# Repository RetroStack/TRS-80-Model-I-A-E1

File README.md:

# TRS-80 Model 1 (Rev A) Replica - E1

This project is a reverse-engineered PCB created to document the mainboard of the iconic TRS-80 Model 1 (Revision A) computer. Released in 1977, Revision A was the first implementation and features some differences compared to later revisions, including a different Z3 selector, a slightly modified video sync circuit, and a lack of support for 8k dynamic RAM.

The entire project is available under the MIT license.

**NOTE:** The PCB has not yet been validated. Once I am able to fully validate the PCB by producing a board and thoroughly testing it, I will make the Gerber files available. Additionally, I will have some PCBs available in my [store](https://shop.retrostack.org).

## Project Details

### Latest Files

In the "Latest" folder, you'll find the most up-to-date design files, including:

- The [full schematics](/Latest/TRS80_Model_I_A_E1_Schematics.pdf) of the E1 replica which is 1:1 to the original G board.

### Implementation

E1 has been implemented using KiCAD 8. The KiCAD project files are included in this repository.

### RetroStack Libraries

To work with this KiCAD project, you'll need the RetroStack libraries for KiCAD. Please [follow this link](https://www.github.com/RetroStack/KiCAD-Libraries) to access and install these libraries.

## Main TRS-80 Model 1 Repository

For additional resources related to the TRS-80 Model 1, be sure to check out the [central page for the TRS-80 Model 1](https://www.github.com/RetroStack/TRS-80-Model-I) on [RetroStack](https://www.github.com/RetroStack).

## Support this Project

RetroStack is passionate about exploring and preserving the legacy of older computer systems. My work involves creating detailed documentation and videos to share the knowledge. I am also dedicated to reviving these classic systems by reimplementing them and offering replacement parts at no cost. If you're keen on supporting this unique project, I invite you to visit my [Patreon page](https://www.patreon.com/RetroStack). Your support would be immensely valuable and greatly appreciated!

## License

This project is licensed under the MIT License - see the [LICENSE](LICENSE) file for details.

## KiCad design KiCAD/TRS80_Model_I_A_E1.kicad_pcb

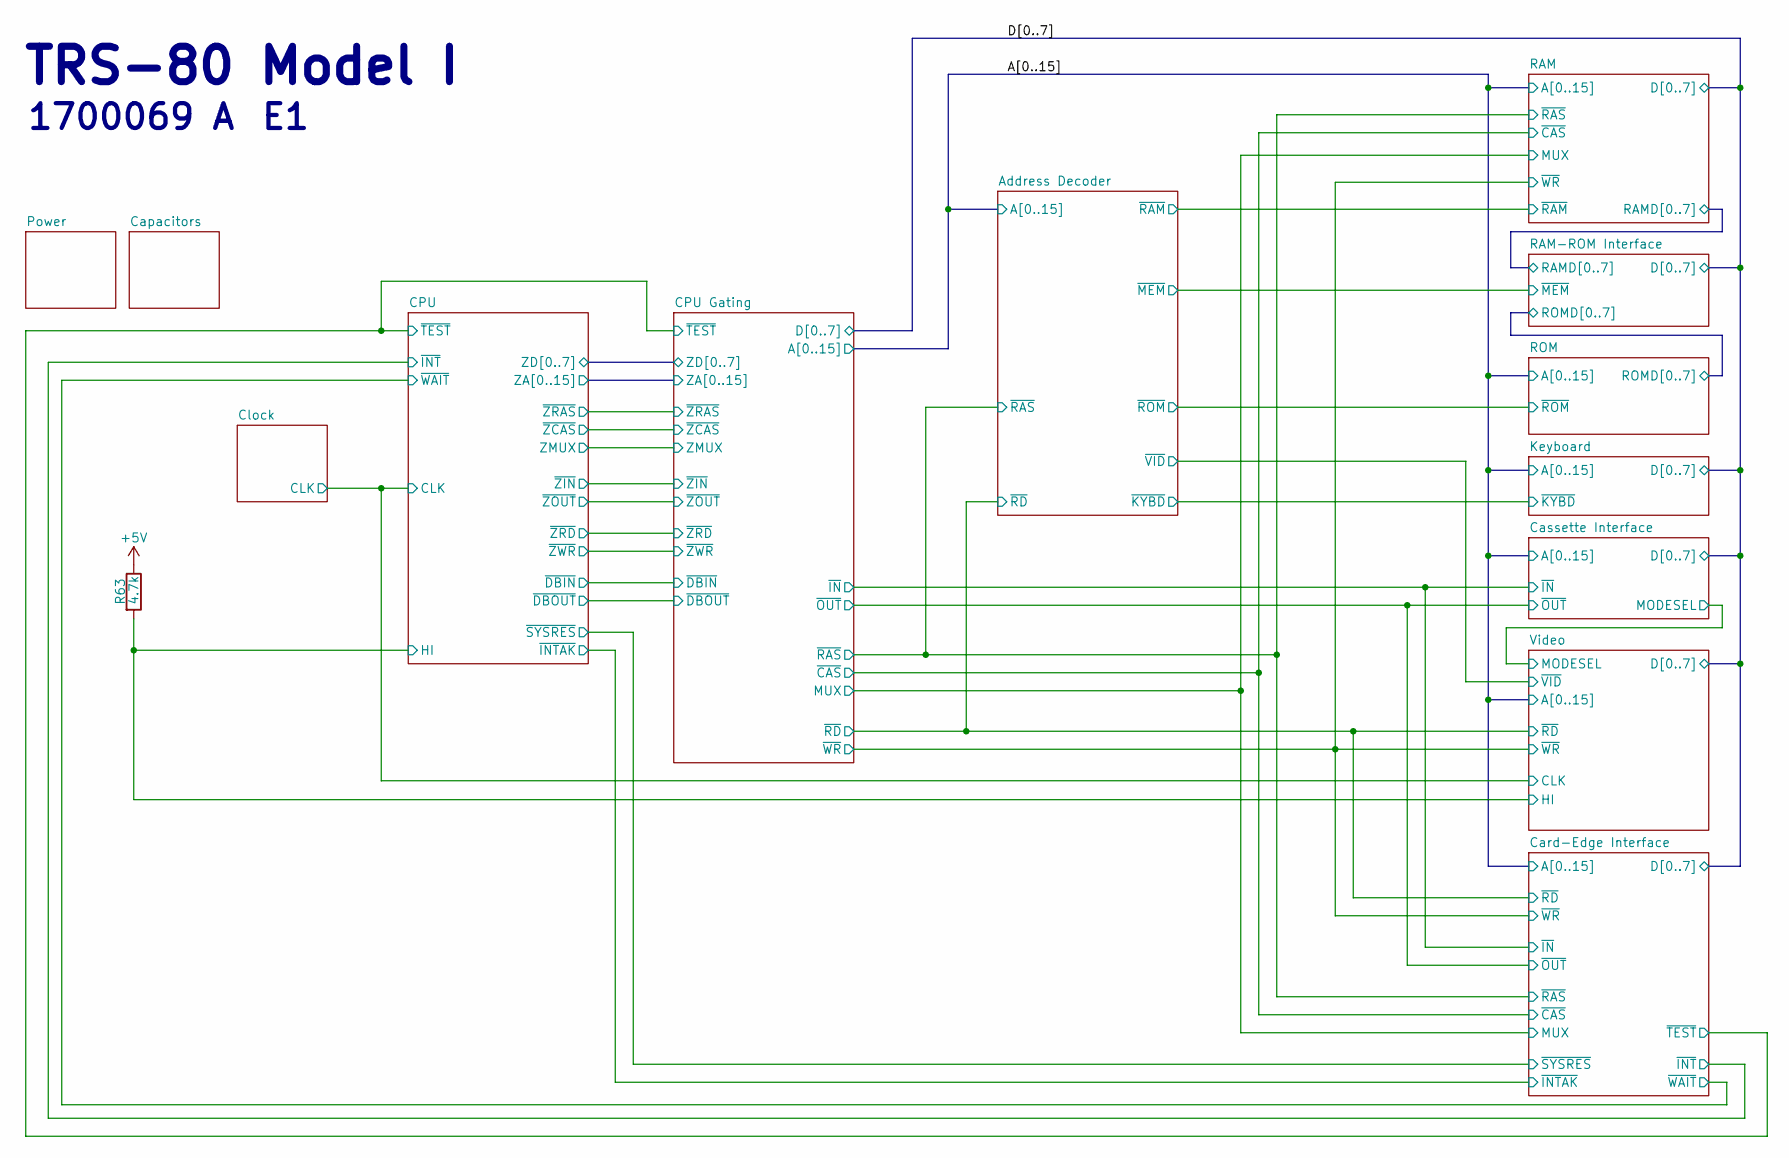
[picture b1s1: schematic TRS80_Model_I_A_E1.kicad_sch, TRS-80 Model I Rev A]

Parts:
R63: 4.7k; TRS80_Model_I_R_0.25W

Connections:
+5V: R63.1; also elsewhere on the board
/CPU/HI: R63.2; also elsewhere on the board

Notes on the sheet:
TRS-80 Model I
1700069 A

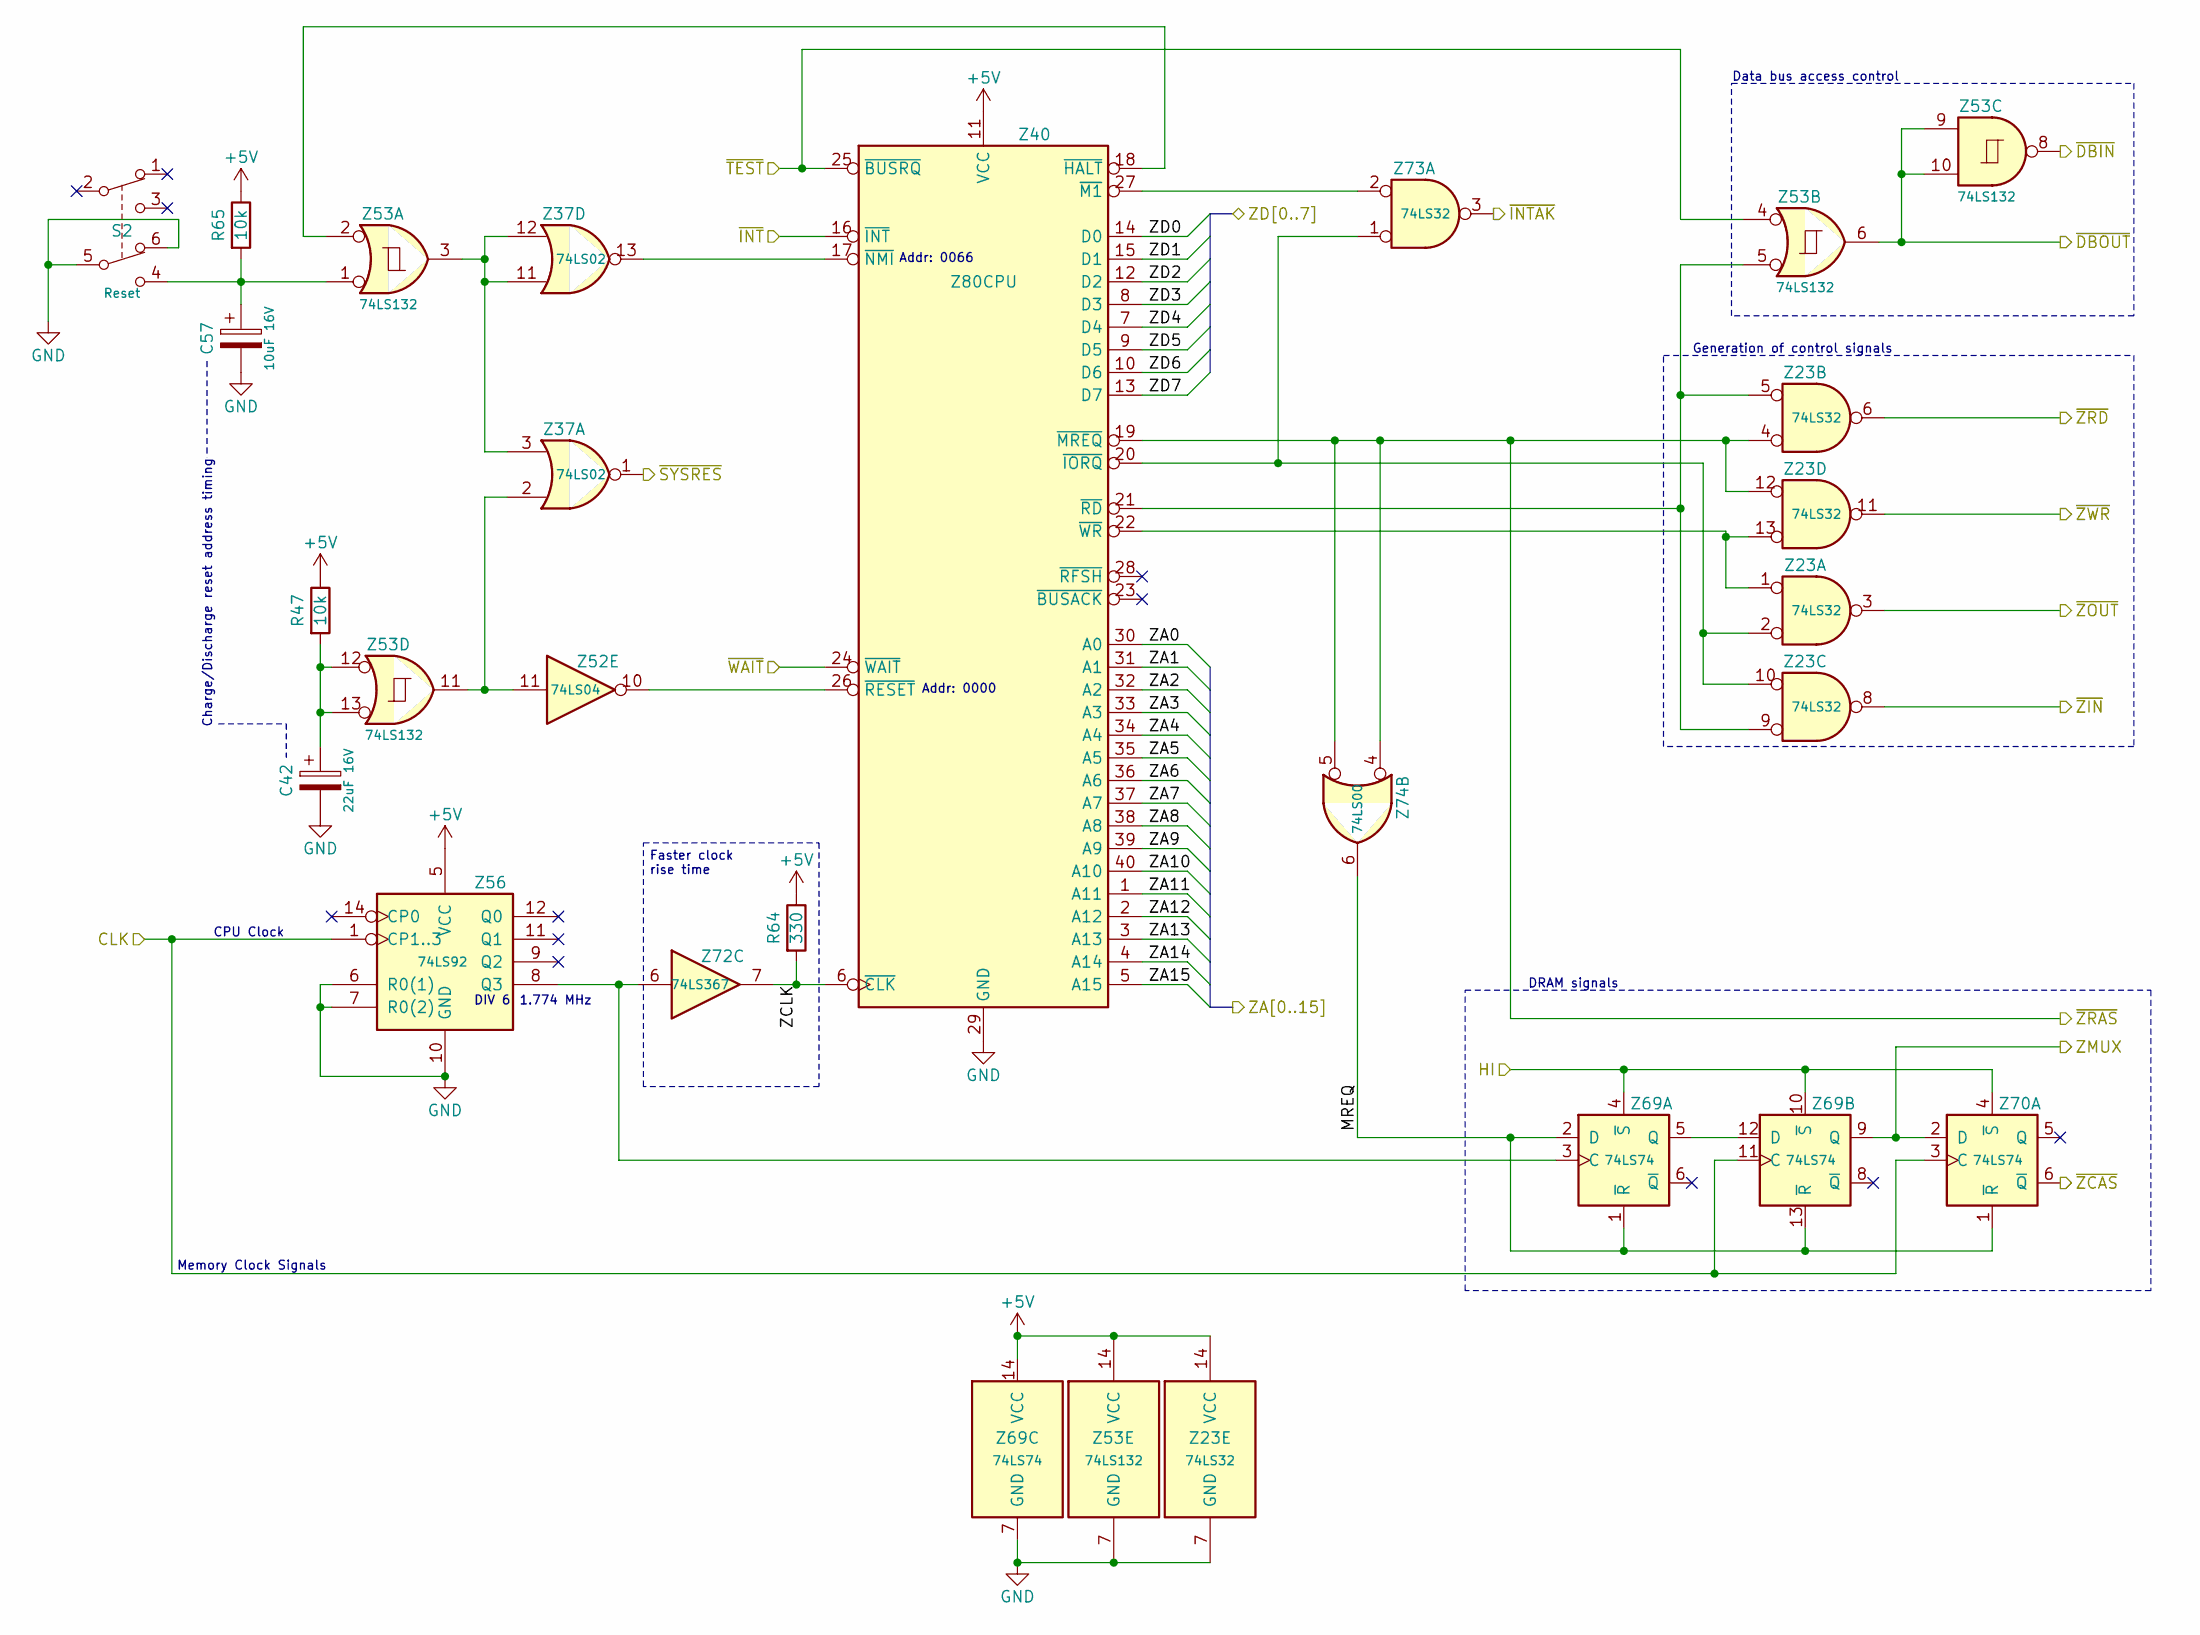
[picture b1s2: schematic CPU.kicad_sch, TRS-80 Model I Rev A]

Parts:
C42: 22uF 16V; TRS80_Model_I_C_Pol_Radial_6.3D_2.5P
C57: 10uF 16V; TRS80_Model_I_C_Pol_Radial_5D_2.5P
R47, R65: 10k; TRS80_Model_I_R_0.25W
R64: 330; TRS80_Model_I_R_0.25W
S2: Reset; TRS80_Model_I_Sw_Small
Z23, Z73: 74LS32; TRS80_Model_I_DIP14
Z37: 74LS02; TRS80_Model_I_DIP14
Z40: Z80CPU; TRS80_Model_I_DIP40
Z52: 74LS04; TRS80_Model_I_DIP14
Z53: 74LS132; TRS80_Model_I_DIP14
Z56: 74LS92; TRS80_Model_I_DIP14
Z69, Z70: 74LS74; TRS80_Model_I_DIP14
Z72: 74LS367; TRS80_Model_I_DIP16
Z74: 74LS00; TRS80_Model_I_DIP14

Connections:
+5V: R47.1, R64.1, R65.1, Z23.14 (VCC), Z40.11 (VCC), Z53.14 (VCC), Z56.5 (VCC), Z69.14 (VCC); also elsewhere on the board
/CPU Gating/ZA0: Z40.30 (A0); also elsewhere on the board
/CPU Gating/ZA1: Z40.31 (A1); also elsewhere on the board
/CPU Gating/ZA2: Z40.32 (A2); also elsewhere on the board
/CPU Gating/ZA3: Z40.33 (A3); also elsewhere on the board
/CPU Gating/ZA4: Z40.34 (A4); also elsewhere on the board
/CPU Gating/ZA5: Z40.35 (A5); also elsewhere on the board
/CPU Gating/ZA6: Z40.36 (A6); also elsewhere on the board
/CPU Gating/ZA7: Z40.37 (A7); also elsewhere on the board
/CPU Gating/ZA8: Z40.38 (A8); also elsewhere on the board
/CPU Gating/ZA9: Z40.39 (A9); also elsewhere on the board
/CPU Gating/ZA10: Z40.40 (A10); also elsewhere on the board
/CPU Gating/ZA11: Z40.1 (A11); also elsewhere on the board
/CPU Gating/ZA12: Z40.2 (A12); also elsewhere on the board
/CPU Gating/ZA13: Z40.3 (A13); also elsewhere on the board
/CPU Gating/ZA14: Z40.4 (A14); also elsewhere on the board
/CPU Gating/ZA15: Z40.5 (A15); also elsewhere on the board
/CPU Gating/ZD0: Z40.14 (D0); also elsewhere on the board
/CPU Gating/ZD1: Z40.15 (D1); also elsewhere on the board
/CPU Gating/ZD2: Z40.12 (D2); also elsewhere on the board
/CPU Gating/ZD3: Z40.8 (D3); also elsewhere on the board
/CPU Gating/ZD4: Z40.7 (D4); also elsewhere on the board
/CPU Gating/ZD5: Z40.9 (D5); also elsewhere on the board
/CPU Gating/ZD6: Z40.10 (D6); also elsewhere on the board
/CPU Gating/ZD7: Z40.13 (D7); also elsewhere on the board
/CPU Gating/ZMUX: Z69.9 (Q), Z70.2 (D); also elsewhere on the board
/CPU Gating/~DBIN: Z53.8; also elsewhere on the board
/CPU Gating/~DBOUT: Z53.6, Z53.9, Z53.10; also elsewhere on the board
/CPU Gating/~TEST: Z40.25 (~BUSRQ), Z53.4; also elsewhere on the board
/CPU Gating/~ZCAS: Z70.6 (~Q); also elsewhere on the board
/CPU Gating/~ZIN: Z23.8; also elsewhere on the board
/CPU Gating/~ZOUT: Z23.3; also elsewhere on the board
/CPU Gating/~ZRAS: Z23.4, Z23.12, Z40.19 (~MREQ), Z74.4, Z74.5; also elsewhere on the board
/CPU Gating/~ZRD: Z23.6; also elsewhere on the board
/CPU Gating/~ZWR: Z23.11; also elsewhere on the board
/CPU/CLK: Z56.1 (CP1..3), Z69.11 (C), Z70.3 (C); also elsewhere on the board
/CPU/HI: Z69.4 (~S), Z69.10 (~S), Z70.4 (~S); also elsewhere on the board
/CPU/MREQ: Z69.1 (~R), Z69.2 (D), Z69.13 (~R), Z70.1 (~R), Z74.6
/CPU/ZCLK: R64.2, Z40.6 (~CLK), Z72.7
/CPU/~INTAK: Z73.3; also elsewhere on the board
/CPU/~INT: Z40.16 (~INT); also elsewhere on the board
/CPU/~SYSRES: Z37.1; also elsewhere on the board
/CPU/~WAIT: Z40.24 (~WAIT); also elsewhere on the board
GND: C42.2, C57.2, S2.5, S2.6, Z23.7 (GND), Z40.29 (GND), Z53.7 (GND), Z56.6 (R0(1)), Z56.7 (R0(2)), Z56.10 (GND), Z69.7 (GND); also elsewhere on the board
unnamed: C42.1, R47.2, Z53.12, Z53.13
unnamed: C57.1, R65.2, S2.4, Z53.1
unnamed: Z37.2, Z52.11, Z53.11
unnamed: Z37.3, Z37.11, Z37.12, Z53.3
unnamed: Z40.18 (~HALT), Z53.2
unnamed: Z23.2, Z23.10, Z40.20 (~IORQ), Z73.1
unnamed: Z40.27 (~M1), Z73.2
unnamed: Z37.13, Z40.17 (~NMI)
unnamed: Z23.5, Z23.9, Z40.21 (~RD), Z53.5
unnamed: Z40.26 (~RESET), Z52.10
unnamed: Z23.1, Z23.13, Z40.22 (~WR)
unnamed: Z56.8 (Q3), Z69.3 (C), Z72.6
unnamed: Z69.5 (Q), Z69.12 (D)

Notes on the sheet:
Data bus access control
DIV 6
Generation of control signals
DRAM signals
1.774 MHz
Faster clock rise time
Memory Clock Signals
CPU Clock
Addr: 0000
Charge/Discharge reset address timing
Addr: 0066

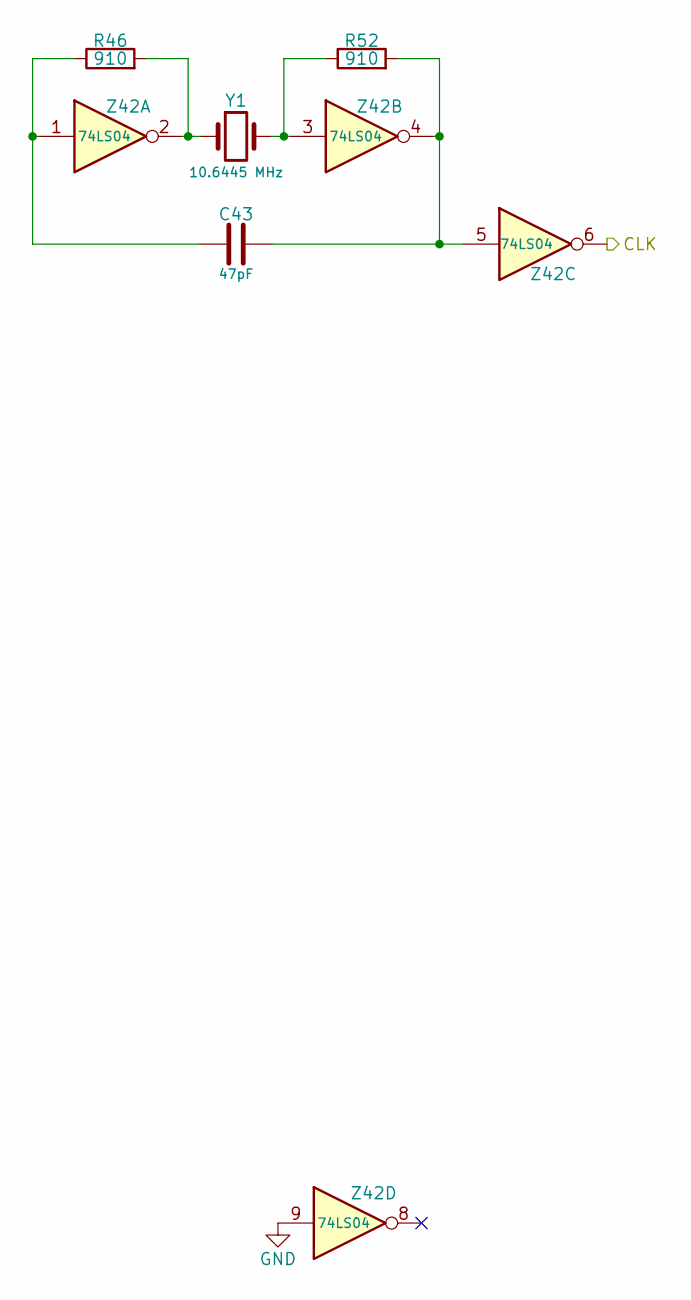
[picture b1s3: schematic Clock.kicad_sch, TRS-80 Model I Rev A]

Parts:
C43: 47pF; TRS80_Model_I_C_Disc_9.5L_4W_6P_Small
R46, R52: 910; TRS80_Model_I_R_0.25W
Y1: 10.6445 MHz; TRS80_Model_I_Crystal
Z42: 74LS04; TRS80_Model_I_DIP14

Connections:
/CPU/CLK: Z42.6; also elsewhere on the board
GND: Z42.9; also elsewhere on the board
unnamed: C43.1, R46.1, Z42.1
unnamed: C43.2, R52.2, Z42.4, Z42.5
unnamed: R46.2, Y1.1, Z42.2
unnamed: R52.1, Y1.2, Z42.3

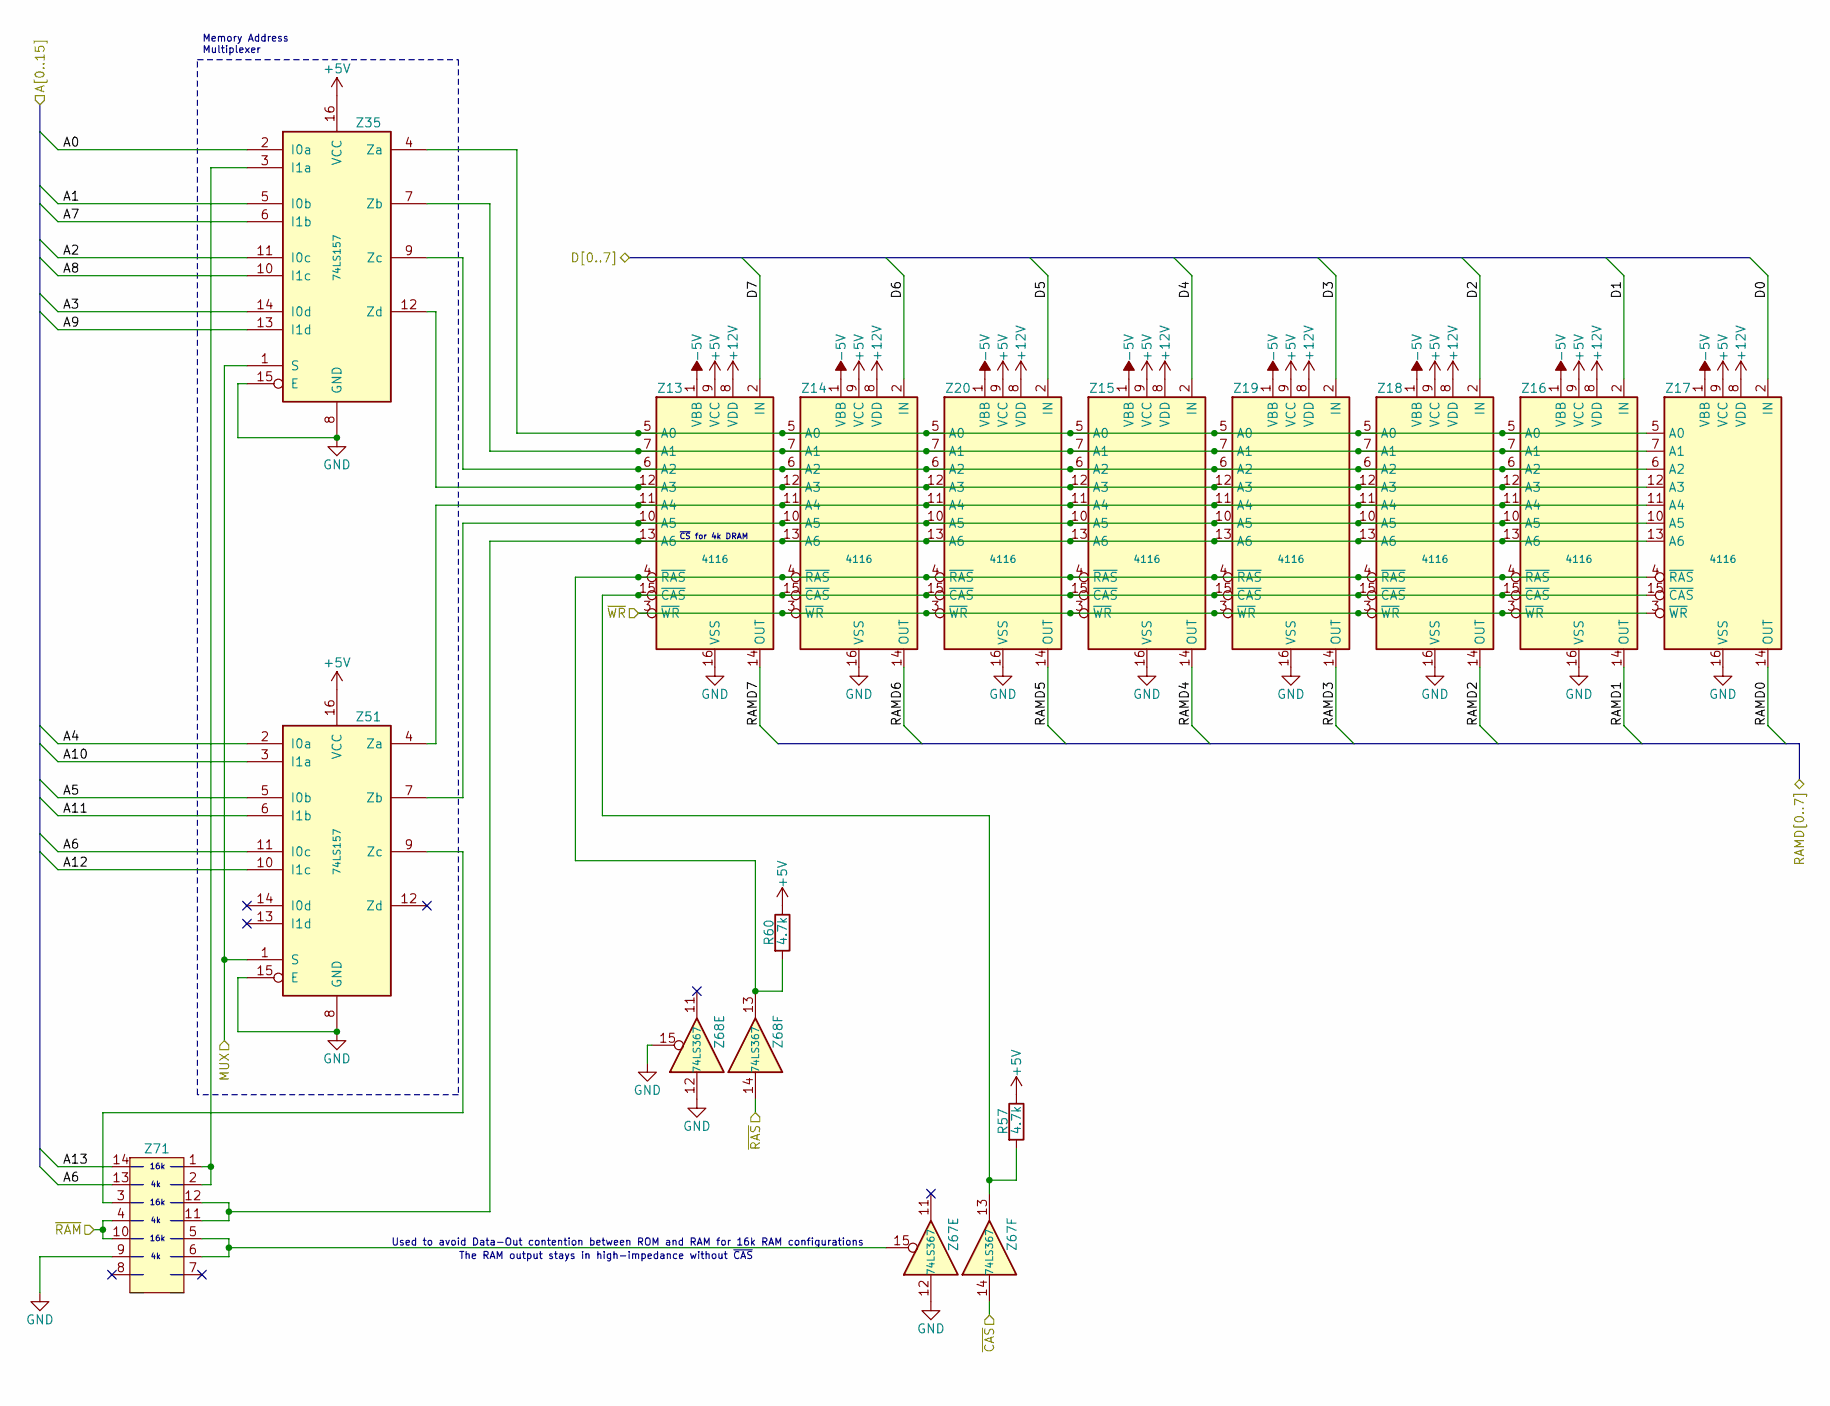
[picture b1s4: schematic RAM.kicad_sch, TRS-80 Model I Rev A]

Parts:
R57, R60: 4.7k; TRS80_Model_I_R_0.25W
Z13, Z14, Z15, Z16, Z17, Z18, Z19, Z20: 4116; TRS80_Model_I_DIP16
Z35, Z51: 74LS157; TRS80_Model_I_DIP16
Z67, Z68: 74LS367; TRS80_Model_I_DIP16
Z71: TRS80_Model_I_DIP14

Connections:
+5V: R57.1, R60.1, Z13.9 (VCC), Z14.9 (VCC), Z15.9 (VCC), Z16.9 (VCC), Z17.9 (VCC), Z18.9 (VCC), Z19.9 (VCC), Z20.9 (VCC), Z35.16 (VCC), Z51.16 (VCC); also elsewhere on the board
+12V: Z13.8 (VDD), Z14.8 (VDD), Z15.8 (VDD), Z16.8 (VDD), Z17.8 (VDD), Z18.8 (VDD), Z19.8 (VDD), Z20.8 (VDD); also elsewhere on the board
-5V: Z13.1 (VBB), Z14.1 (VBB), Z15.1 (VBB), Z16.1 (VBB), Z17.1 (VBB), Z18.1 (VBB), Z19.1 (VBB), Z20.1 (VBB); also elsewhere on the board
/A0: Z35.2 (I0a); also elsewhere on the board
/A1: Z35.5 (I0b); also elsewhere on the board
/A2: Z35.11 (I0c); also elsewhere on the board
/A3: Z35.14 (I0d); also elsewhere on the board
/A4: Z51.2 (I0a); also elsewhere on the board
/A5: Z51.5 (I0b); also elsewhere on the board
/A6: Z51.11 (I0c), Z71.13; also elsewhere on the board
/A7: Z35.6 (I1b); also elsewhere on the board
/A8: Z35.10 (I1c); also elsewhere on the board
/A9: Z35.13 (I1d); also elsewhere on the board
/A10: Z51.3 (I1a); also elsewhere on the board
/A11: Z51.6 (I1b); also elsewhere on the board
/A12: Z51.10 (I1c); also elsewhere on the board
/A13: Z71.14; also elsewhere on the board
/Address Decoder/~RAM: Z71.4, Z71.10; also elsewhere on the board
/Address Decoder/~RAS: Z68.14; also elsewhere on the board
/CPU Gating/MUX: Z35.1 (S), Z51.1 (S); also elsewhere on the board
/CPU Gating/~CAS: Z67.14; also elsewhere on the board
/CPU Gating/~WR: Z13.3 (~WR), Z14.3 (~WR), Z15.3 (~WR), Z16.3 (~WR), Z17.3 (~WR), Z18.3 (~WR), Z19.3 (~WR), Z20.3 (~WR); also elsewhere on the board
/D0: Z17.2 (IN); also elsewhere on the board
/D1: Z16.2 (IN); also elsewhere on the board
/D2: Z18.2 (IN); also elsewhere on the board
/D3: Z19.2 (IN); also elsewhere on the board
/D4: Z15.2 (IN); also elsewhere on the board
/D5: Z20.2 (IN); also elsewhere on the board
/D6: Z14.2 (IN); also elsewhere on the board
/D7: Z13.2 (IN); also elsewhere on the board
/RAM-ROM Interface/ROMD0: Z17.14 (OUT); also elsewhere on the board
/RAM-ROM Interface/ROMD1: Z16.14 (OUT); also elsewhere on the board
/RAM-ROM Interface/ROMD2: Z18.14 (OUT); also elsewhere on the board
/RAM-ROM Interface/ROMD3: Z19.14 (OUT); also elsewhere on the board
/RAM-ROM Interface/ROMD4: Z15.14 (OUT); also elsewhere on the board
/RAM-ROM Interface/ROMD5: Z20.14 (OUT); also elsewhere on the board
/RAM-ROM Interface/ROMD6: Z14.14 (OUT); also elsewhere on the board
/RAM-ROM Interface/ROMD7: Z13.14 (OUT); also elsewhere on the board
GND: Z13.16 (VSS), Z14.16 (VSS), Z15.16 (VSS), Z16.16 (VSS), Z17.16 (VSS), Z18.16 (VSS), Z19.16 (VSS), Z20.16 (VSS), Z35.8 (GND), Z35.15 (E), Z51.8 (GND), Z51.15 (E), Z67.12, Z68.12, Z68.15, Z71.9; also elsewhere on the board
unnamed: Z13.5 (A0), Z14.5 (A0), Z15.5 (A0), Z16.5 (A0), Z17.5 (A0), Z18.5 (A0), Z19.5 (A0), Z20.5 (A0), Z35.4 (Za)
unnamed: Z13.7 (A1), Z14.7 (A1), Z15.7 (A1), Z16.7 (A1), Z17.7 (A1), Z18.7 (A1), Z19.7 (A1), Z20.7 (A1), Z35.7 (Zb)
unnamed: Z13.6 (A2), Z14.6 (A2), Z15.6 (A2), Z16.6 (A2), Z17.6 (A2), Z18.6 (A2), Z19.6 (A2), Z20.6 (A2), Z35.9 (Zc)
unnamed: Z13.12 (A3), Z14.12 (A3), Z15.12 (A3), Z16.12 (A3), Z17.12 (A3), Z18.12 (A3), Z19.12 (A3), Z20.12 (A3), Z35.12 (Zd)
unnamed: Z13.11 (A4), Z14.11 (A4), Z15.11 (A4), Z16.11 (A4), Z17.11 (A4), Z18.11 (A4), Z19.11 (A4), Z20.11 (A4), Z51.4 (Za)
unnamed: Z13.10 (A5), Z14.10 (A5), Z15.10 (A5), Z16.10 (A5), Z17.10 (A5), Z18.10 (A5), Z19.10 (A5), Z20.10 (A5), Z51.7 (Zb)
unnamed: Z13.13 (A6), Z14.13 (A6), Z15.13 (A6), Z16.13 (A6), Z17.13 (A6), Z18.13 (A6), Z19.13 (A6), Z20.13 (A6), Z71.11, Z71.12
unnamed: R57.2, Z13.15 (~CAS), Z14.15 (~CAS), Z15.15 (~CAS), Z16.15 (~CAS), Z17.15 (~CAS), Z18.15 (~CAS), Z19.15 (~CAS), Z20.15 (~CAS), Z67.13
unnamed: R60.2, Z13.4 (~RAS), Z14.4 (~RAS), Z15.4 (~RAS), Z16.4 (~RAS), Z17.4 (~RAS), Z18.4 (~RAS), Z19.4 (~RAS), Z20.4 (~RAS), Z68.13
unnamed: Z35.3 (I1a), Z71.1, Z71.2
unnamed: Z51.9 (Zc), Z71.3
unnamed: Z67.15, Z71.5, Z71.6

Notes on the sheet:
Memory Address Multiplexer
The RAM output stays in high-impedance without ~{CAS}
16k
Used to avoid Data-Out contention between ROM and RAM for 16k RAM configurations
~{CS} for 4k DRAM

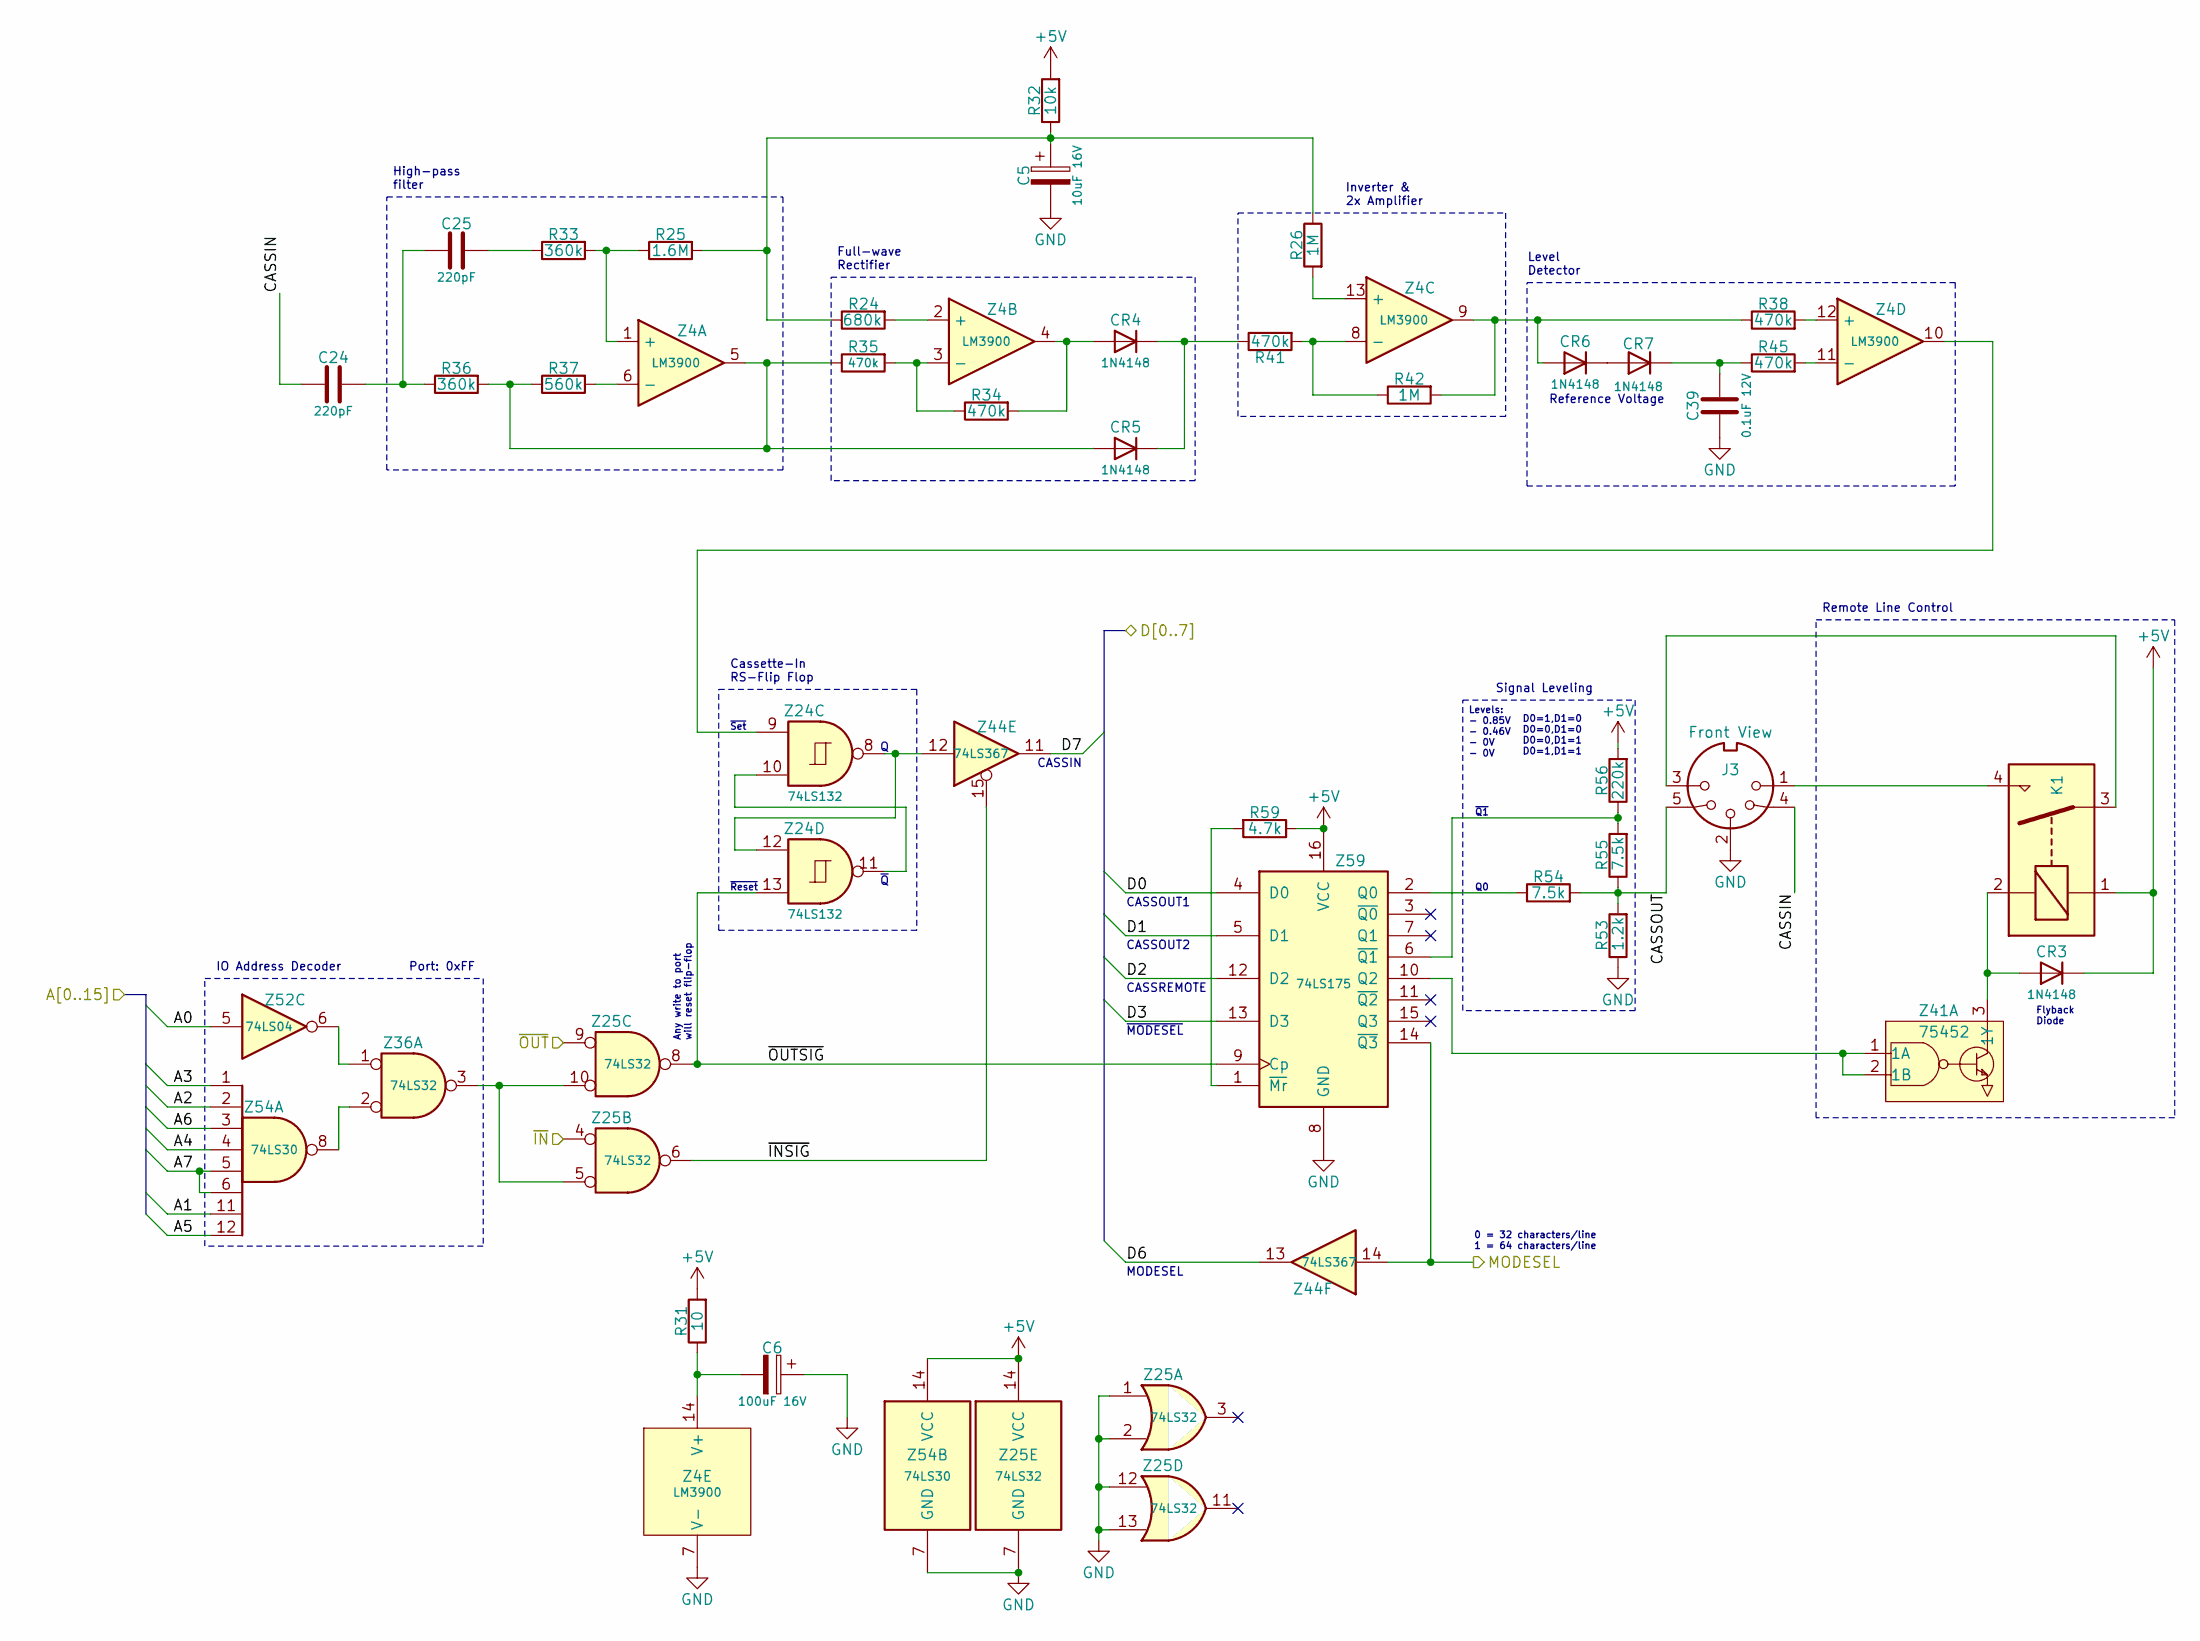
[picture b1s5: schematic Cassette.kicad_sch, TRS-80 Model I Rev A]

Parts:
C5: 10uF 16V; TRS80_Model_I_C_Pol_Radial_5D_2.5P
C6: 100uF 16V; TRS80_Model_I_C_Pol_Radial_10D_5P
C24, C25: 220pF; TRS80_Model_I_C_Disc_9.5L_4W_6P_Small
C39: 0.1uF 12V; TRS80_Model_I_C_Disc_9.5L_4W_6P_Small
CR3, CR4, CR5, CR6, CR7: 1N4148; TRS80_Model_I_D
J3: Front View; TRS80_Model_I_DIN5
K1: Relay_SPST-NO; TRS80_Model_I_Relay
R24: 680k; TRS80_Model_I_R_0.25W
R25: 1.6M; TRS80_Model_I_R_0.25W
R26, R42: 1M; TRS80_Model_I_R_0.25W
R31: 10; TRS80_Model_I_R_0.25W
R32: 10k; TRS80_Model_I_R_0.25W
R33, R36: 360k; TRS80_Model_I_R_0.25W
R34, R35, R38, R41, R45: 470k; TRS80_Model_I_R_0.25W
R37: 560k; TRS80_Model_I_R_0.25W
R53: 1.2k; TRS80_Model_I_R_0.25W
R54, R55: 7.5k; TRS80_Model_I_R_0.25W
R56: 220k; TRS80_Model_I_R_0.25W
R59: 4.7k; TRS80_Model_I_R_0.25W
Z4: LM3900; TRS80_Model_I_DIP14
Z24: 74LS132; TRS80_Model_I_DIP14
Z25, Z36: 74LS32; TRS80_Model_I_DIP14
Z41: 75452; TRS80_Model_I_DIP8
Z44: 74LS367; TRS80_Model_I_DIP16
Z52: 74LS04; TRS80_Model_I_DIP14
Z54: 74LS30; TRS80_Model_I_DIP14
Z59: 74LS175; TRS80_Model_I_DIP16

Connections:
+5V: CR3.1 (K), K1.1, R31.2, R32.2, R56.2, R59.1, Z25.14 (VCC), Z54.14 (VCC), Z59.16 (VCC); also elsewhere on the board
/A0: Z52.5; also elsewhere on the board
/A1: Z54.11; also elsewhere on the board
/A2: Z54.2; also elsewhere on the board
/A3: Z54.1; also elsewhere on the board
/A4: Z54.4; also elsewhere on the board
/A5: Z54.12; also elsewhere on the board
/A6: Z54.3; also elsewhere on the board
/A7: Z54.5, Z54.6; also elsewhere on the board
/CPU Gating/~IN: Z25.4; also elsewhere on the board
/CPU Gating/~OUT: Z25.9; also elsewhere on the board
/Cassette Interface/CASSIN: C24.1, J3.4
/Cassette Interface/CASSOUT: J3.5, R53.2, R54.2, R55.1
/Cassette Interface/MODESEL: Z44.14, Z59.14 (~Q3); also elsewhere on the board
/Cassette Interface/~INSIG: Z25.6, Z44.15
/Cassette Interface/~OUTSIG: Z24.13, Z25.8, Z59.9 (Cp)
/D0: Z59.4 (D0); also elsewhere on the board
/D1: Z59.5 (D1); also elsewhere on the board
/D2: Z59.12 (D2); also elsewhere on the board
/D3: Z59.13 (D3); also elsewhere on the board
/D6: Z44.13; also elsewhere on the board
/D7: Z44.11; also elsewhere on the board
GND: C5.2, C6.1, C39.1, J3.2, R53.1, Z4.7 (V-), Z25.1, Z25.2, Z25.7 (GND), Z25.12, Z25.13, Z54.7 (GND), Z59.8 (GND); also elsewhere on the board
unnamed: C5.1, R24.1, R25.2, R26.1, R32.1
unnamed: C24.2, C25.1, R36.1
unnamed: C25.2, R33.1
unnamed: CR3.2 (A), K1.2, Z41.3 (1Y)
unnamed: CR4.2 (A), R34.2, Z4.4
unnamed: CR4.1 (K), CR5.1 (K), R41.1
unnamed: CR5.2 (A), R35.1, R36.2, R37.1, Z4.5
unnamed: CR6.2 (A), R38.1, R42.2, Z4.9
unnamed: CR6.1 (K), CR7.2 (A)
unnamed: C39.2, CR7.1 (K), R45.1
unnamed: J3.1, K1.4
unnamed: J3.3, K1.3
unnamed: R25.1, R33.2, Z4.1 (+)
unnamed: R37.2, Z4.6 (-)
unnamed: R24.2, Z4.2 (+)
unnamed: R34.1, R35.2, Z4.3 (-)
unnamed: R26.2, Z4.13 (+)
unnamed: R41.2, R42.1, Z4.8 (-)
unnamed: R38.2, Z4.12 (+)
unnamed: R45.2, Z4.11 (-)
unnamed: C6.2, R31.1, Z4.14 (V+)
unnamed: Z4.10, Z24.9
unnamed: Z24.10, Z24.11
unnamed: Z24.8, Z24.12, Z44.12
unnamed: Z25.5, Z25.10, Z36.3
unnamed: Z36.1, Z52.6
unnamed: Z36.2, Z54.8
unnamed: Z41.1 (1A), Z41.2 (1B), Z59.10 (Q2)
unnamed: R54.1, Z59.2 (Q0)
unnamed: R59.2, Z59.1 (~Mr)
unnamed: R55.2, R56.1, Z59.6 (~Q1)

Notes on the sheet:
~{MODESEL}
0 = 32 characters/line 1 = 64 characters/line
Full-wave Rectifier
Level Detector
High-pass filter
Reference Voltage
Any write to port will reset flip-flop
IO Address Decoder
CASSREMOTE
Remote Line Control
Port: 0xFF
~{Q}
CASSOUT1
Flyback Diode
Signal Leveling
CASSOUT2
CASSIN
MODESEL
Cassette-In RS-Flip Flop
~{Q1}
Levels: - 0.85V - 0.46V - 0V - 0V
Inverter & 2x Amplifier
~{Reset}
~{Set}
D0=1,D1=0 D0=0,D1=0 D0=0,D1=1 D0=1,D1=1

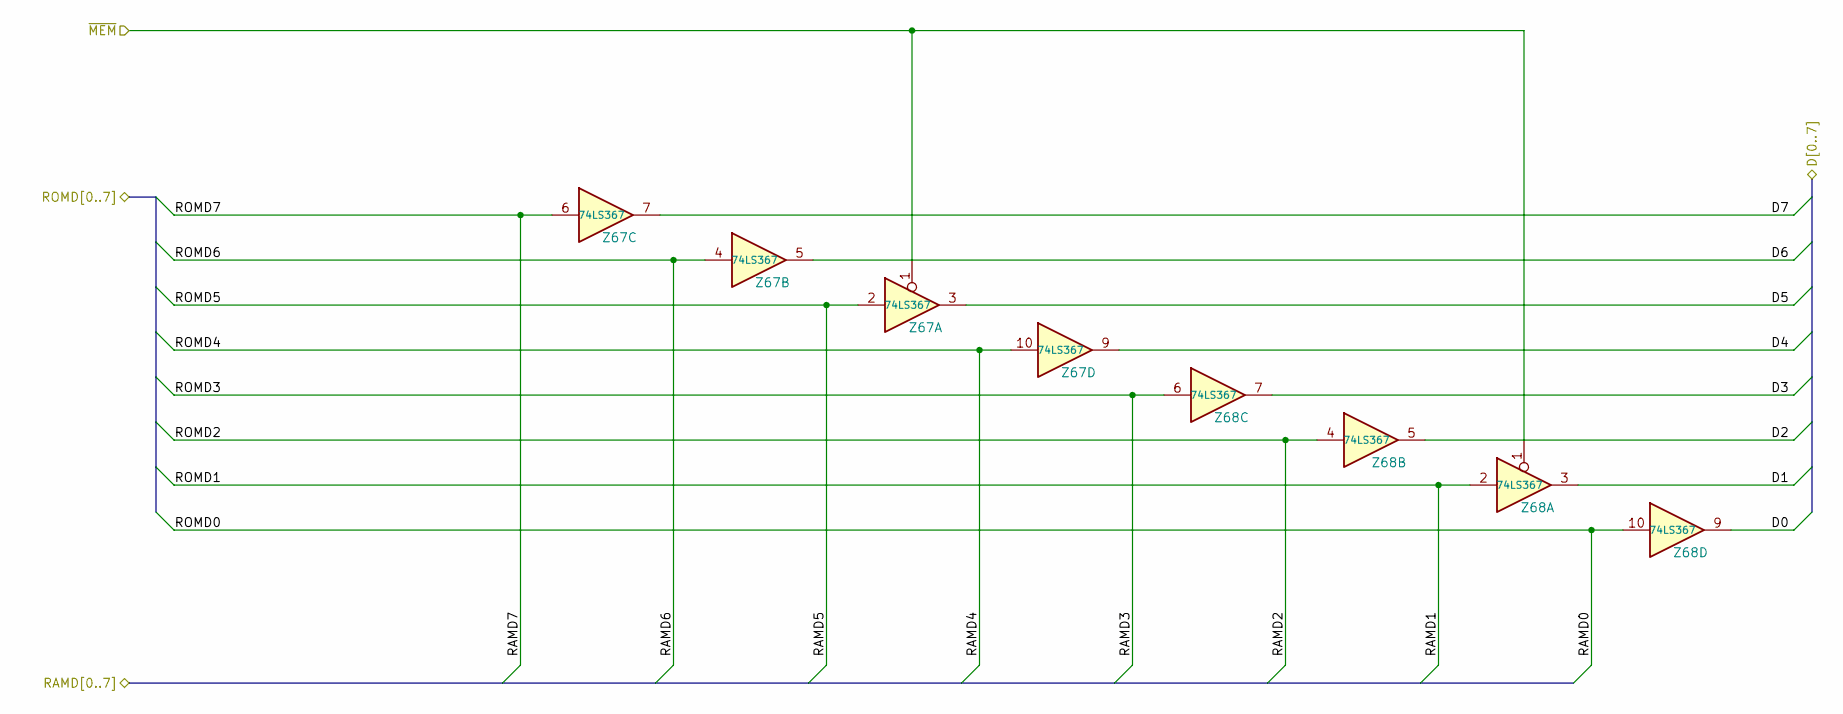
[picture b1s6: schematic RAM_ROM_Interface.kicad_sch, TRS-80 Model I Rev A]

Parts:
Z67, Z68: 74LS367; TRS80_Model_I_DIP16

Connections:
/Address Decoder/~MEM: Z67.1, Z68.1; also elsewhere on the board
/D0: Z68.9; also elsewhere on the board
/D1: Z68.3; also elsewhere on the board
/D2: Z68.5; also elsewhere on the board
/D3: Z68.7; also elsewhere on the board
/D4: Z67.9; also elsewhere on the board
/D5: Z67.3; also elsewhere on the board
/D6: Z67.5; also elsewhere on the board
/D7: Z67.7; also elsewhere on the board
/RAM-ROM Interface/ROMD0: Z68.10; also elsewhere on the board
/RAM-ROM Interface/ROMD1: Z68.2; also elsewhere on the board
/RAM-ROM Interface/ROMD2: Z68.4; also elsewhere on the board
/RAM-ROM Interface/ROMD3: Z68.6; also elsewhere on the board
/RAM-ROM Interface/ROMD4: Z67.10; also elsewhere on the board
/RAM-ROM Interface/ROMD5: Z67.2; also elsewhere on the board
/RAM-ROM Interface/ROMD6: Z67.4; also elsewhere on the board
/RAM-ROM Interface/ROMD7: Z67.6; also elsewhere on the board
